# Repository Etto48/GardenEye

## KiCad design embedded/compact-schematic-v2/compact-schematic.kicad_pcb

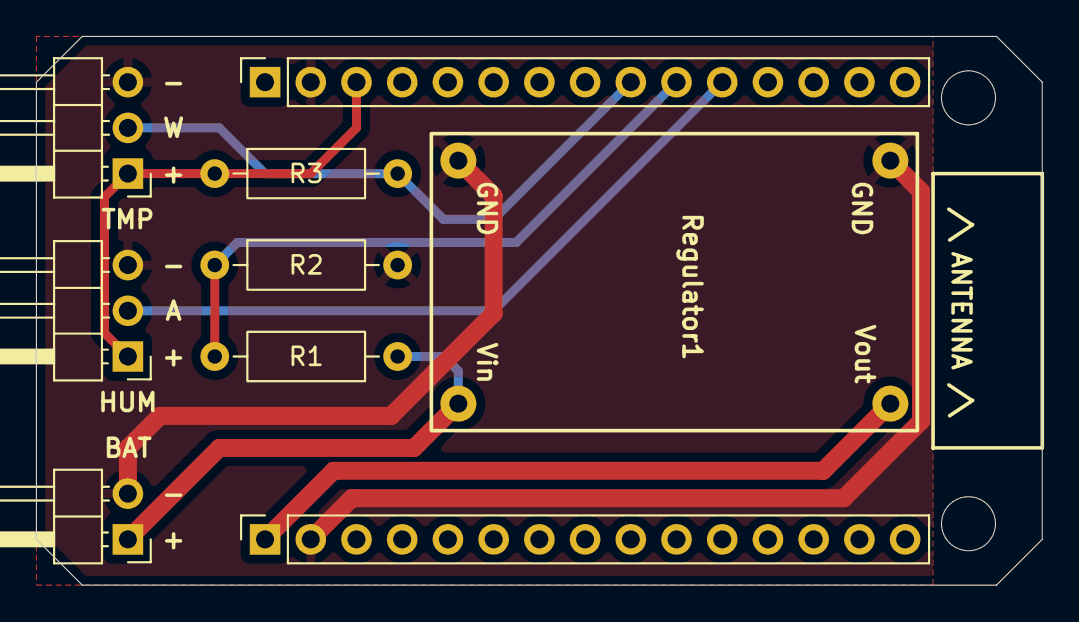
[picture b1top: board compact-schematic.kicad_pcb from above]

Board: 2 copper layers, 55.9 x 30.5 mm, 9 parts (0 on the bottom side), 7 nets.

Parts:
BAT: PinHeader_1x02_P2.54mm_Horizontal
BoardLeft: PinSocket_1x15_P2.54mm_Vertical
BoardRight: PinSocket_1x15_P2.54mm_Vertical
HUM: PinHeader_1x03_P2.54mm_Horizontal
R1, R2: 1M; R_Axial_DIN0207_L6.3mm_D2.5mm_P10.16mm_Horizontal
R3: 4.7k; R_Axial_DIN0207_L6.3mm_D2.5mm_P10.16mm_Horizontal
Regulator1: BuckBoost3.3V_0.85A
TMP: PinHeader_1x03_P2.54mm_Horizontal

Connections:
3.3V: BoardLeft.1, Regulator1.2 (Vout+)
BAT: BoardRight.10, R1.2, R2.1
BAT+: BAT.1, R1.1, Regulator1.0 (Vin+)
GND: BAT.2, BoardLeft.2, BoardRight.2, HUM.3, R2.2, Regulator1.1 (Vin-), TMP.3
HUM: BoardRight.11, HUM.2
SEN: BoardRight.3, HUM.1, R3.1, TMP.1
TMP: BoardRight.9, R3.2, TMP.2

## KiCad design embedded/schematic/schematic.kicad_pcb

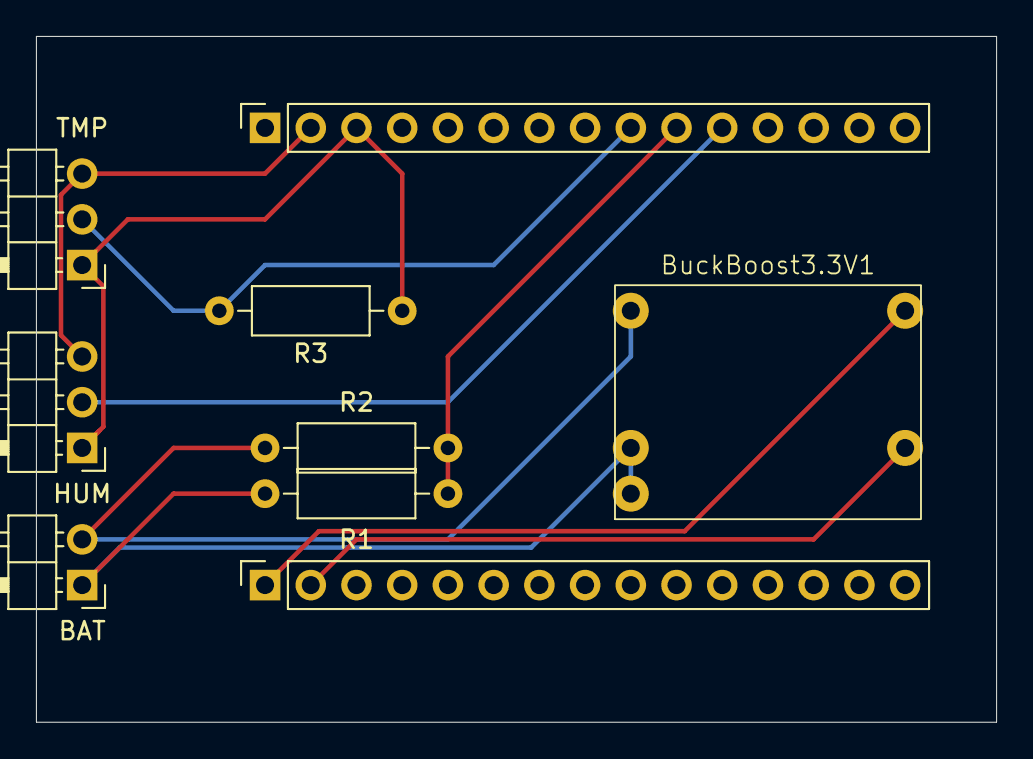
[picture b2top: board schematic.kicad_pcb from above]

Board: 2 copper layers, 53.3 x 38.1 mm, 7 parts (0 on the bottom side), 5 nets.

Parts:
BAT: PinHeader_1x02_P2.54mm_Horizontal
BuckBoost3.3V1: BuckBoost3.3V
HUM: PinHeader_1x03_P2.54mm_Horizontal
R1, R2: 1M; R_Axial_DIN0207_L6.3mm_D2.5mm_P10.16mm_Horizontal
R3: 4.7k; R_Axial_DIN0207_L6.3mm_D2.5mm_P10.16mm_Horizontal
TMP: PinHeader_1x03_P2.54mm_Horizontal

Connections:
BAT: R1.2, R2.1
BAT+: BAT.+, BuckBoost3.3V1.2 (Vin+), BuckBoost3.3V1.3 (EN), R1.1
GND: BAT.-, BuckBoost3.3V1.1 (Vin-), HUM.-, R2.2, TMP.-
SEN: HUM.+, R3.1, TMP.+
TMP: R3.2, TMP.D

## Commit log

2025-09-10 added reverse proxy in prod
2025-09-10 Implemented basic frontend
2025-09-10 moved proxy in dev
2025-09-10 added cards
2025-09-10 new icons, better style and fixed bug with db transactions
2025-09-10 actual fetch of data for info
2025-09-10 added graphs
2025-09-10 new endpoint for registration
2025-09-10 added 404
2025-09-12 Refactored css
2025-09-13 Better responsive code
2025-09-17 Added schematic and settings. added sensor images
2025-09-17 Added board firmware
2025-09-19 Updated schematics
2025-09-19 better settings and reindented some files
2025-09-19 fixed stupid warning
2025-09-20 fixed warning
2025-09-21 Fixed bug with thermometer
2025-09-22 Fixed bugs and added sync
2025-09-22 added settings page
2025-09-22 Better settings
2025-09-22 fixed some styles and responsive layout
2025-09-22 fixed style of favicon
2025-09-23 Added icons to nav
2025-09-23 merged navs
2025-09-23 changed hostname
2025-09-24 real prod version
2025-09-24 Added args to compose and info to the readme
2025-09-24 updated npm packages
2025-09-24 updated run for frontend
2025-09-24 fixed warns
2025-09-24 overridden timescaledb-tune memory limits
2025-09-25 refactored arduino files
2025-09-25 Added compact schematic
2025-10-25 updated compact schematic
2025-10-27 updated schematic
2025-11-06 Add support for prod-detach and prod-stop modes in compose script
2025-11-06 Fixed compose script
2025-11-06 updated package lock
2025-11-29 Started testing v2 board
